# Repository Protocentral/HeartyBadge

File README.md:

# ProtoCentral HeartyBadge

HeartyBadge is simply our popular HeartyPatch single-lead ECG & Heart-rate variability (HRV) monitoring device made into a badge in time for DEFCON 26, where I presented about our HealthyPi open-source patient monitor. We think of HeartyBadge as a ECG and HRV development board, on a badge. 

The following are the main features of the HeartyBadge: 
* Single-lead ECG monitoring with the MAX30003 
* 2 gold-plated pads on the PCB act as electrodes 
* ESP32 with PCB antenna supporting Bluetooth & Wi-Fi 
* 144 APA102 RGB addressable LEDs (most of them in a matrix) 
* On-board Li-Ion battery with charging 
* USB for charging, code upload as well as debugging 

More information is available on our Hackaday project page at: https://hackaday.io/project/160846-heartybadge

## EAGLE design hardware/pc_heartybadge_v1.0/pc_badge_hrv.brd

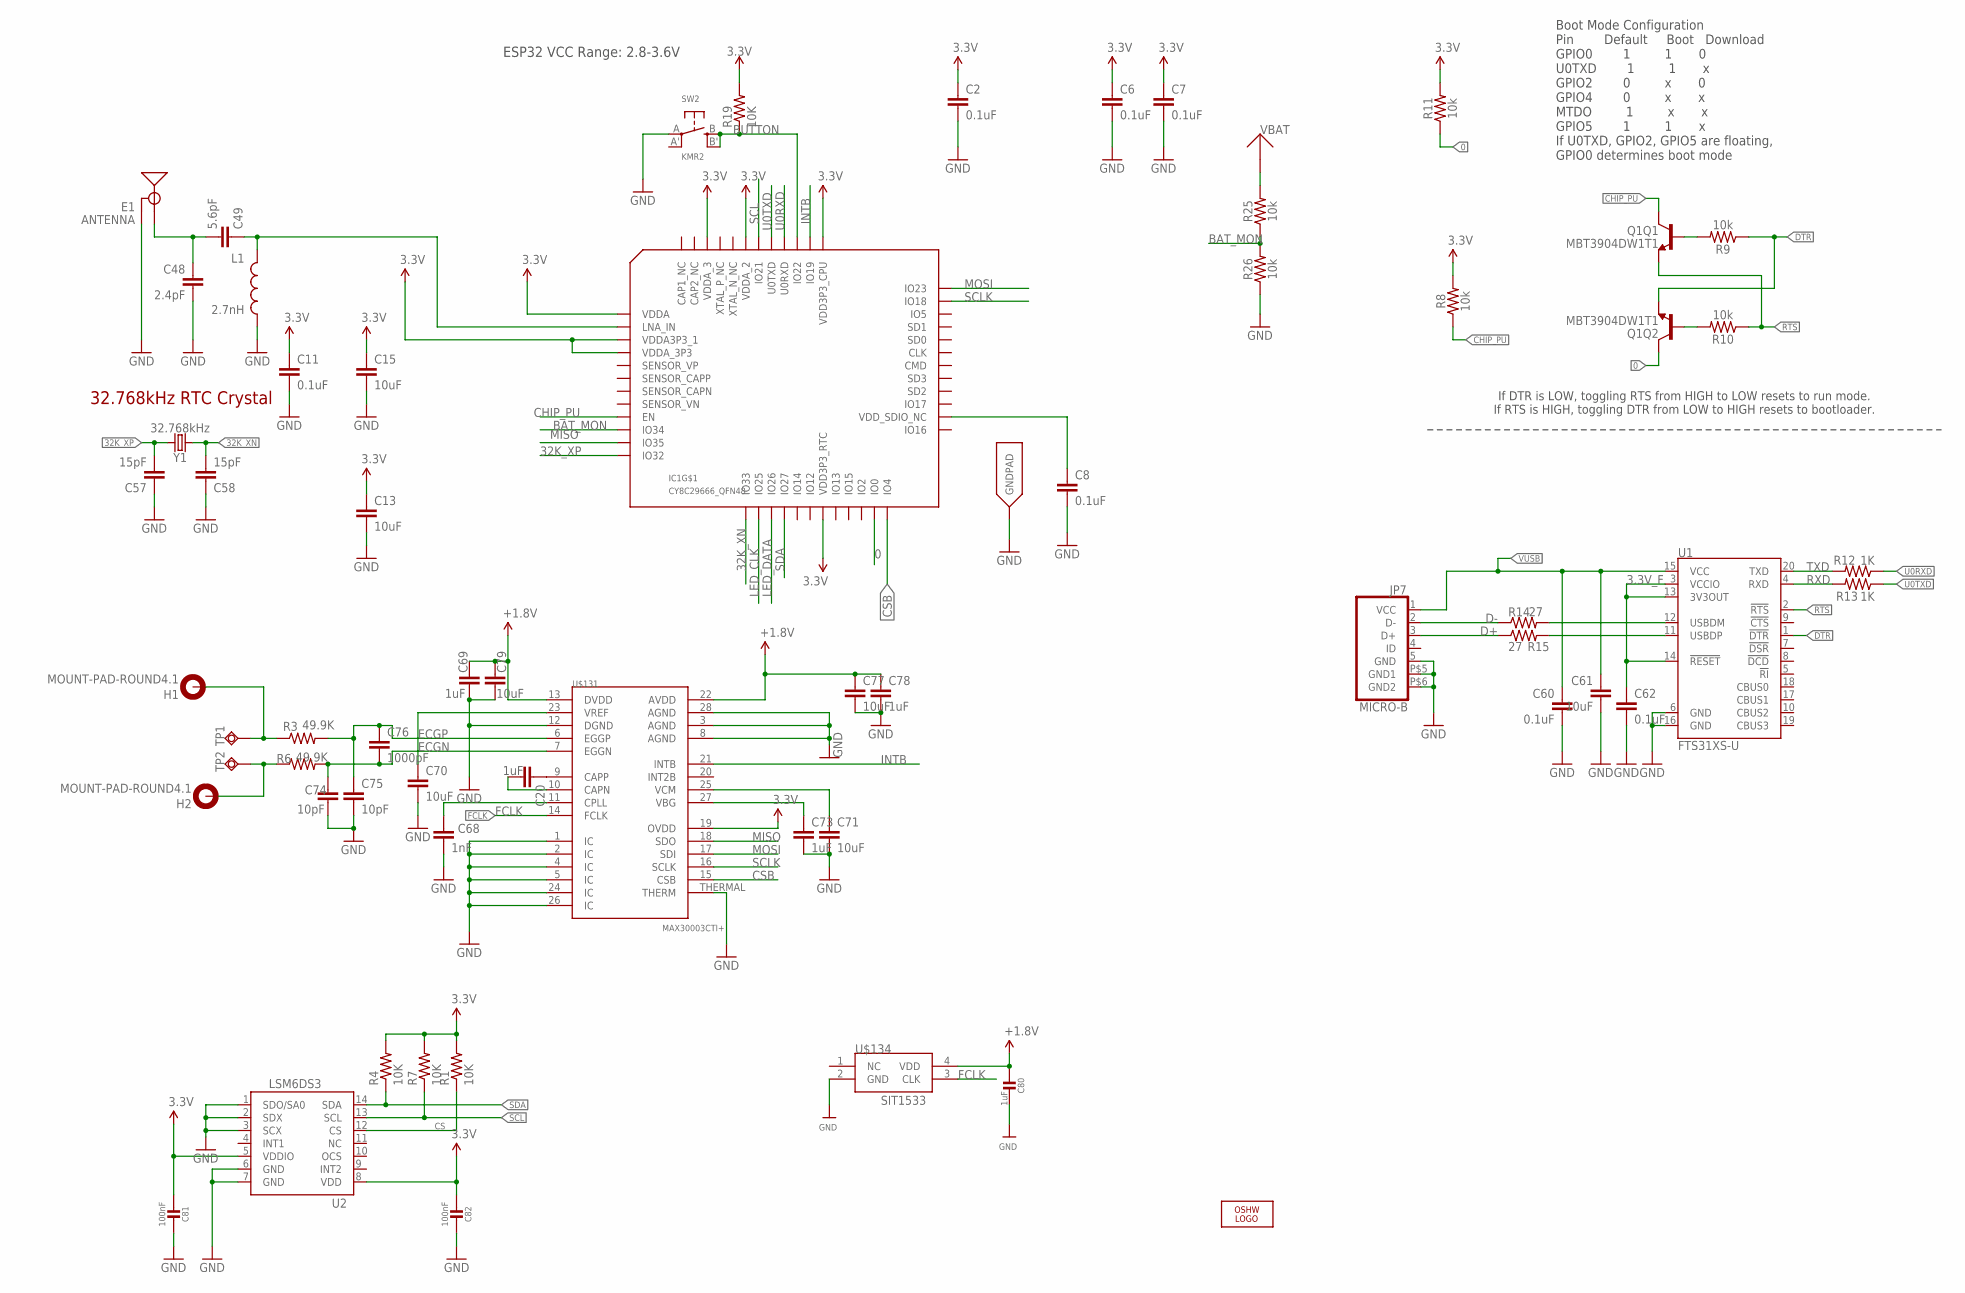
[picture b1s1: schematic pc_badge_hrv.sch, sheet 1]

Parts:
C2, C6, C7, C8, C11: 0.1uF; 0402
C13, C15: 10uF; 0603
C20, C69, C73, C78: 1uF; C0402
C48: 2.4pF; 0603
C49: 5.6pF; 0603
C57, C58: 15pF; 0603
C60, C62: 0.1uF; C0402
C61: 10uF; C0805
C68: 1nF; C0402
C70, C71, C77, C79: 10uF; C0402
C74, C75: 10pF; C0402
C76: 1000pF; C0402
C80: 1uF; _0402
C81, C82: 100nF; _0402
E1: ANTENNA; TRACE_ANTENNA_2.4GHZ_25.7MM_TUNED
H1, H2: MOUNT-PAD-ROUND4.1; 4,1-PAD
IC1: CY8C29666_QFN48; QFN48
JP7: MICRO-B
L1: 2.7nH; 0603
LOGO3: OSHW_LOGO_FILLX0200-NT; OSHW_FILLX200_NOTEXT
Q1: MBT3904DW1T1; SC70-6
R1, R4, R7: 10K; 0402-RES
R3, R6: 49.9K; 0402-RES
R8, R9, R10, R11, R25, R26: 10k; 0603
R12, R13: 1K; R0402
R14, R15: 27; R0402
R19: 10K; R0402
SW2: KMR2; BTN_KMR2_4.6X2.8
TP1, TP2: TPSQTP11R; TP11R
U1: FTS31XS-U; SSOP20_L
U2: LSM6DS3; LGA14L
U$131: MAX30003CTI+; QFN-28
U$134: SIT1533
Y1: 32.768kHz; CRYSTAL-SMD-3.2X1.5MM

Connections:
0: IC1.23 (IO0), Q1.6 (C), R11.1
3.3V: C2.1, C6.1, C7.1, C11.1, C13.1, C15.1, C81.1, C82.1, IC1.1 (VDDA), IC1.3 (VDDA3P3_1), IC1.4 (VDDA_3P3), IC1.19 (VDD3P3_RTC), IC1.37 (VDD3P3_CPU), IC1.43 (VDDA_2), IC1.46 (VDDA_3), R1.2, R4.2, R7.2, R8.2, R11.2, R19.2, U2.5 (VDDIO), U2.8 (VDD), U$131.19 (OVDD); also elsewhere on the board
3.3V_F: C62.1, U1.3 (VCCIO), U1.13 (3V3OUT), U1.14 (!RESET)
32K_XN: C58.2, IC1.13 (IO33), Y1.P$2 (2)
32K_XP: C57.2, IC1.12 (IO32), Y1.P$1 (1)
+1.8V: C69.1, C77.1, C78.1, C79.1, C80.1, U$131.13 (DVDD), U$131.22 (AVDD), U$134.4 (VDD)
BAT_MON: IC1.10 (IO34), R25.1, R26.2
BUTTON: IC1.39 (IO22), R19.1, SW2.B (S), SW2.B' (S1)
CHIP_PU: IC1.9 (EN), Q1.3 (C), R8.1
CS: R1.1, U2.12 (CS)
CSB: IC1.24 (IO4), U$131.15 (CSB)
D+: JP7.3 (D+), R15.1
D-: JP7.2 (D-), R14.1
DTR: Q1.1 (E), R9.1, U1.1 (!DTR)
ECGN: C74.1, C76.2, R6.2, U$131.7 (EGGN)
ECGP: C75.1, C76.1, R3.2, U$131.6 (EGGP)
ECG_N: H2.B4,1, R6.1, TP2.TP
ECG_P: H1.B4,1, R3.1, TP1.TP
FCLK: U$131.14 (FCLK), U$134.3 (CLK)
GND: C2.2, C6.2, C7.2, C8.2, C11.2, C13.2, C15.2, C48.2, C57.1, C58.1, C60.2, C61.2, C62.2, C68.2, C69.2, C70.2, C71.2, C73.2, C74.2, C75.2, C77.2, C78.2, C79.2, C80.2, C81.2, C82.2, E1.GND, E1.GND2 (GND), IC1.EXP (GNDPAD), JP7.5 (GND), JP7.P$5 (GND1), JP7.P$6 (GND2), L1.2, R26.1, SW2.A, U1.6 (GND), U1.16 (GND), U2.1 (SDO/SA0), U2.2 (SDX), U2.3 (SCX), U2.6 (GND), U2.7 (GND), U$131.1 (IC), U$131.2 (IC), U$131.3 (AGND), U$131.4 (IC), U$131.5 (IC), U$131.8 (AGND), U$131.12 (DGND), U$131.24 (IC), U$131.26 (IC), U$131.28 (AGND), U$131.THERMAL (THERM), U$134.2 (GND); also elsewhere on the board
INTB: IC1.38 (IO19), U$131.21 (INTB)
IO12: IC1.18 (IO12)
LED_CLK: IC1.14 (IO25); also elsewhere on the board
LED_DATA: IC1.15 (IO26); also elsewhere on the board
LNA_IN: C49.1, IC1.2 (LNA_IN), L1.1
MISO: IC1.11 (IO35), U$131.18 (SDO)
MOSI: IC1.36 (IO23), U$131.17 (SDI)
unnamed: C8.1, IC1.26 (VDD_SDIO_NC)
unnamed: Q1.5 (B), R9.2
unnamed: Q1.2 (B), R10.2
unnamed: R14.2, U1.12 (USBDM)
unnamed: R15.2, U1.11 (USBDP)
unnamed: C68.1, U$131.11 (CPLL)
unnamed: C20.1, U$131.9 (CAPP)
unnamed: C20.2, U$131.10 (CAPN)
unnamed: C70.1, U$131.23 (VREF)
unnamed: C71.1, U$131.25 (VCM)
unnamed: C73.1, U$131.27 (VBG)
RTS: Q1.4 (E), R10.1, U1.2 (!RTS)
RXD: R13.2, U1.4 (RXD)
SCL: IC1.42 (IO21), R7.1, U2.13 (SCL)
SCLK: IC1.35 (IO18), U$131.16 (SCLK)
SDA: IC1.16 (IO27), R4.1, U2.14 (SDA)
SENSOR_CAPN: IC1.7 (SENSOR_CAPN)
TRACE_ANT2: C48.1, C49.2, E1.ANT (SIGNAL)
TXD: R12.2, U1.20 (TXD)
U0RXD: IC1.40 (U0RXD), R12.1
U0TXD: IC1.41 (U0TXD), R13.1
VBAT: R25.2; also elsewhere on the board
VUSB: C60.1, C61.1, JP7.1 (VCC), U1.15 (VCC); also elsewhere on the board

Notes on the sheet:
Boot Mode Configuration Pin Default Boot Download GPIO0 1 1 0 U0TXD 1 1 x GPIO2 0 x 0 GPIO4 0 x x MTDO 1 x x GPIO5 1 1 x If U0TXD, GPIO2, GPIO5 are floating, GPIO0 determines boot mode
32.768kHz RTC Crystal
ESP32 VCC Range: 2.8-3.6V
If DTR is LOW, toggling RTS from HIGH to LOW resets to run mode. If RTS is HIGH, toggling DTR from LOW to HIGH resets to bootloader.

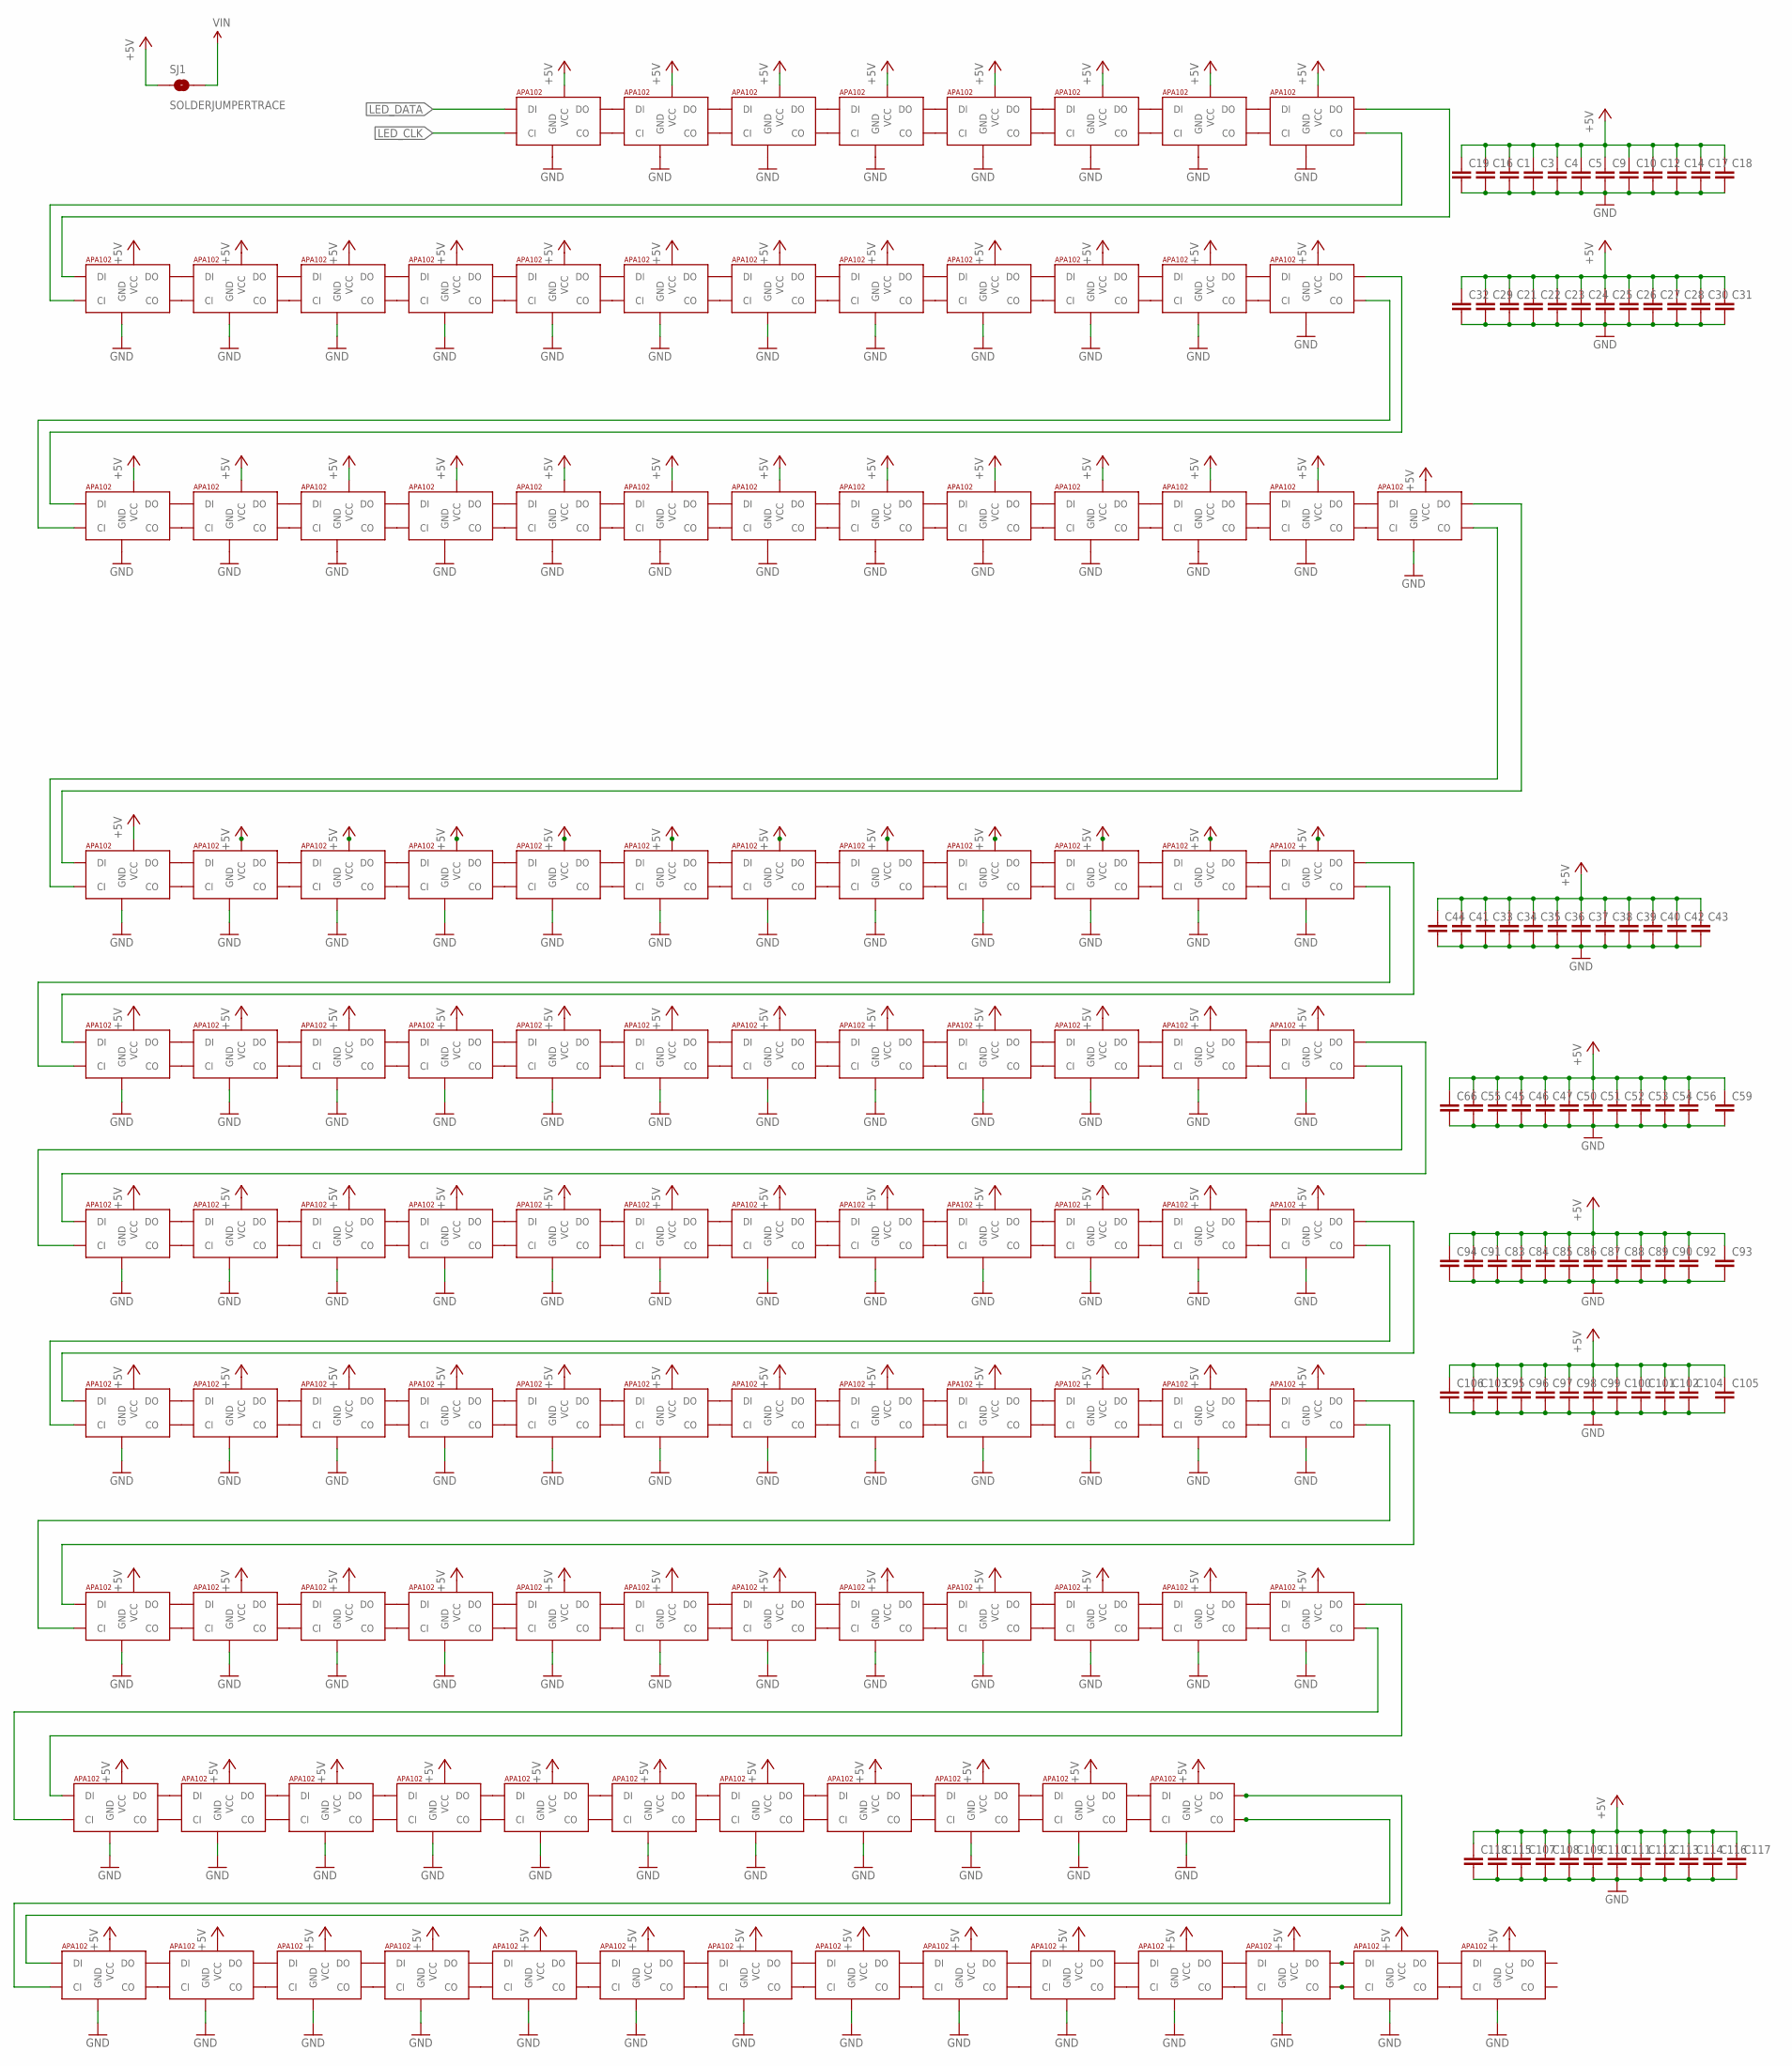
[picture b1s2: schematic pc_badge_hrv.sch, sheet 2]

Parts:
C1, C3, C4, C5, C9, C10, C12, C14, C16, C17, C18, C19, C21, C22, C23, C24, C25, C26, C27, C28, C29, C30, C31, C32, C33, C34, C35, C36, C37, C38, C39, C40, C41, C42, C43, C44, C45, C46, C47, C50, C51, C52, C53, C54, C55, C56, C59, C66, C83, C84, C85, C86, C87, C88, C89, C90, C91, C92, C93, C94, C95, C96, C97, C98, C99, C100, C101, C102, C103, C104, C105, C106, C107, C108, C109, C110, C111, C112, C113, C114, C115, C116, C117, C118: C-EUC0402K; C0402K
SJ1: SOLDERJUMPERTRACE; SJ_2S-TRACE
U$9, U$10, U$11, U$12, U$13, U$14, U$15, U$18, U$19, U$20, U$21, U$22, U$24, U$25, U$27, U$28, U$29, U$30, U$31, U$32, U$33, U$34, U$35, U$36, U$37, U$38, U$39, U$40, U$41, U$42, U$43, U$44, U$45, U$46, U$47, U$48, U$49, U$50, U$51, U$52, U$53, U$54, U$55, U$56, U$57, U$58, U$59, U$60, U$61, U$62, U$63, U$64, U$65, U$66, U$67, U$68, U$69, U$70, U$71, U$72, U$73, U$74, U$75, U$76, U$77, U$78, U$79, U$80, U$81, U$82, U$83, U$84, U$85, U$86, U$87, U$88, U$89, U$90, U$91, U$92, U$93, U$94, U$95, U$96, U$97, U$98, U$99, U$100, U$101, U$102, U$103, U$104, U$105, U$106, U$107, U$108, U$109, U$110, U$111, U$112, U$113, U$114, U$115, U$116, U$117, U$118, U$119, U$120, U$121, U$122, U$123, U$124, U$125, U$126, U$127, U$128, U$129, U$130: APA1022020; APA102_2020

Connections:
+5V: C1.1, C3.1, C4.1, C5.1, C9.1, C10.1, C12.1, C14.1, C16.1, C17.1, C18.1, C19.1, C21.1, C22.1, C23.1, C24.1, C25.1, C26.1, C27.1, C28.1, C29.1, C30.1, C31.1, C32.1, C33.1, C34.1, C35.1, C36.1, C37.1, C38.1, C39.1, C40.1, C41.1, C42.1, C43.1, C44.1, C45.1, C46.1, C47.1, C50.1, C51.1, C52.1, C53.1, C54.1, C55.1, C56.1, C59.1, C66.1, C83.1, C84.1, C85.1, C86.1, C87.1, C88.1, C89.1, C90.1, C91.1, C92.1, C93.1, C94.1, C95.1, C96.1, C97.1, C98.1, C99.1, C100.1, C101.1, C102.1, C103.1, C104.1, C105.1, C106.1, C107.1, C108.1, C109.1, C110.1, C111.1, C112.1, C113.1, C114.1, C115.1, C116.1, C117.1, C118.1, SJ1.1, U$9.V_CC (VCC), U$10.V_CC (VCC), U$11.V_CC (VCC), U$12.V_CC (VCC), U$13.V_CC (VCC), U$14.V_CC (VCC), U$15.V_CC (VCC), U$18.V_CC (VCC), U$19.V_CC (VCC), U$20.V_CC (VCC), U$21.V_CC (VCC), U$22.V_CC (VCC), U$24.V_CC (VCC), U$25.V_CC (VCC), U$27.V_CC (VCC), U$28.V_CC (VCC), U$29.V_CC (VCC), U$30.V_CC (VCC), U$31.V_CC (VCC), U$32.V_CC (VCC), U$33.V_CC (VCC), U$34.V_CC (VCC), U$35.V_CC (VCC), U$36.V_CC (VCC), U$37.V_CC (VCC), U$38.V_CC (VCC), U$39.V_CC (VCC), U$40.V_CC (VCC), U$41.V_CC (VCC), U$42.V_CC (VCC), U$43.V_CC (VCC), U$44.V_CC (VCC), U$45.V_CC (VCC), U$46.V_CC (VCC), U$47.V_CC (VCC), U$48.V_CC (VCC), U$49.V_CC (VCC), U$50.V_CC (VCC), U$51.V_CC (VCC), U$52.V_CC (VCC), U$53.V_CC (VCC), U$54.V_CC (VCC), U$55.V_CC (VCC), U$56.V_CC (VCC), U$57.V_CC (VCC), U$58.V_CC (VCC), U$59.V_CC (VCC), U$60.V_CC (VCC), U$61.V_CC (VCC), U$62.V_CC (VCC), U$63.V_CC (VCC), U$64.V_CC (VCC), U$65.V_CC (VCC), U$66.V_CC (VCC), U$67.V_CC (VCC), U$68.V_CC (VCC), U$69.V_CC (VCC), U$70.V_CC (VCC), U$71.V_CC (VCC), U$72.V_CC (VCC), U$73.V_CC (VCC), U$74.V_CC (VCC), U$75.V_CC (VCC), U$76.V_CC (VCC), U$77.V_CC (VCC), U$78.V_CC (VCC), U$79.V_CC (VCC), U$80.V_CC (VCC), U$81.V_CC (VCC), U$82.V_CC (VCC), U$83.V_CC (VCC), U$84.V_CC (VCC), U$85.V_CC (VCC), U$86.V_CC (VCC), U$87.V_CC (VCC), U$88.V_CC (VCC), U$89.V_CC (VCC), U$90.V_CC (VCC), U$91.V_CC (VCC), U$92.V_CC (VCC), U$93.V_CC (VCC), U$94.V_CC (VCC), U$95.V_CC (VCC), U$96.V_CC (VCC), U$97.V_CC (VCC), U$98.V_CC (VCC), U$99.V_CC (VCC), U$100.V_CC (VCC), U$101.V_CC (VCC), U$102.V_CC (VCC), U$103.V_CC (VCC), U$104.V_CC (VCC), U$105.V_CC (VCC), U$106.V_CC (VCC), U$107.V_CC (VCC), U$108.V_CC (VCC), U$109.V_CC (VCC), U$110.V_CC (VCC), U$111.V_CC (VCC), U$112.V_CC (VCC), U$113.V_CC (VCC), U$114.V_CC (VCC), U$115.V_CC (VCC), U$116.V_CC (VCC), U$117.V_CC (VCC), U$118.V_CC (VCC), U$119.V_CC (VCC), U$120.V_CC (VCC), U$121.V_CC (VCC), U$122.V_CC (VCC), U$123.V_CC (VCC), U$124.V_CC (VCC), U$125.V_CC (VCC), U$126.V_CC (VCC), U$127.V_CC (VCC), U$128.V_CC (VCC), U$129.V_CC (VCC), U$130.V_CC (VCC)
GND: C1.2, C3.2, C4.2, C5.2, C9.2, C10.2, C12.2, C14.2, C16.2, C17.2, C18.2, C19.2, C21.2, C22.2, C23.2, C24.2, C25.2, C26.2, C27.2, C28.2, C29.2, C30.2, C31.2, C32.2, C33.2, C34.2, C35.2, C36.2, C37.2, C38.2, C39.2, C40.2, C41.2, C42.2, C43.2, C44.2, C45.2, C46.2, C47.2, C50.2, C51.2, C52.2, C53.2, C54.2, C55.2, C56.2, C59.2, C66.2, C83.2, C84.2, C85.2, C86.2, C87.2, C88.2, C89.2, C90.2, C91.2, C92.2, C93.2, C94.2, C95.2, C96.2, C97.2, C98.2, C99.2, C100.2, C101.2, C102.2, C103.2, C104.2, C105.2, C106.2, C107.2, C108.2, C109.2, C110.2, C111.2, C112.2, C113.2, C114.2, C115.2, C116.2, C117.2, C118.2, U$9.GND, U$10.GND, U$11.GND, U$12.GND, U$13.GND, U$14.GND, U$15.GND, U$18.GND, U$19.GND, U$20.GND, U$21.GND, U$22.GND, U$24.GND, U$25.GND, U$27.GND, U$28.GND, U$29.GND, U$30.GND, U$31.GND, U$32.GND, U$33.GND, U$34.GND, U$35.GND, U$36.GND, U$37.GND, U$38.GND, U$39.GND, U$40.GND, U$41.GND, U$42.GND, U$43.GND, U$44.GND, U$45.GND, U$46.GND, U$47.GND, U$48.GND, U$49.GND, U$50.GND, U$51.GND, U$52.GND, U$53.GND, U$54.GND, U$55.GND, U$56.GND, U$57.GND, U$58.GND, U$59.GND, U$60.GND, U$61.GND, U$62.GND, U$63.GND, U$64.GND, U$65.GND, U$66.GND, U$67.GND, U$68.GND, U$69.GND, U$70.GND, U$71.GND, U$72.GND, U$73.GND, U$74.GND, U$75.GND, U$76.GND, U$77.GND, U$78.GND, U$79.GND, U$80.GND, U$81.GND, U$82.GND, U$83.GND, U$84.GND, U$85.GND, U$86.GND, U$87.GND, U$88.GND, U$89.GND, U$90.GND, U$91.GND, U$92.GND, U$93.GND, U$94.GND, U$95.GND, U$96.GND, U$97.GND, U$98.GND, U$99.GND, U$100.GND, U$101.GND, U$102.GND, U$103.GND, U$104.GND, U$105.GND, U$106.GND, U$107.GND, U$108.GND, U$109.GND, U$110.GND, U$111.GND, U$112.GND, U$113.GND, U$114.GND, U$115.GND, U$116.GND, U$117.GND, U$118.GND, U$119.GND, U$120.GND, U$121.GND, U$122.GND, U$123.GND, U$124.GND, U$125.GND, U$126.GND, U$127.GND, U$128.GND, U$129.GND, U$130.GND; also elsewhere on the board
LED_CLK: U$9.C_IN (CI); also elsewhere on the board
LED_DATA: U$9.D_IN (DI); also elsewhere on the board
unnamed: U$104.D_OUT (DO), U$119.D_IN (DI)
unnamed: U$104.CL_OUT (CO), U$119.C_IN (CI)
unnamed: U$9.D_OUT (DO), U$10.D_IN (DI)
unnamed: U$9.CL_OUT (CO), U$10.C_IN (CI)
unnamed: U$11.D_OUT (DO), U$12.D_IN (DI)
unnamed: U$11.CL_OUT (CO), U$12.C_IN (CI)
unnamed: U$12.D_OUT (DO), U$13.D_IN (DI)
unnamed: U$12.CL_OUT (CO), U$13.C_IN (CI)
unnamed: U$13.D_OUT (DO), U$14.D_IN (DI)
unnamed: U$13.CL_OUT (CO), U$14.C_IN (CI)
unnamed: U$14.D_OUT (DO), U$15.D_IN (DI)
unnamed: U$14.CL_OUT (CO), U$15.C_IN (CI)
unnamed: U$15.D_OUT (DO), U$18.D_IN (DI)
unnamed: U$15.CL_OUT (CO), U$18.C_IN (CI)
unnamed: U$10.D_OUT (DO), U$11.D_IN (DI)
unnamed: U$10.CL_OUT (CO), U$11.C_IN (CI)
unnamed: U$19.D_OUT (DO), U$20.D_IN (DI)
unnamed: U$19.CL_OUT (CO), U$20.C_IN (CI)
unnamed: U$20.D_OUT (DO), U$21.D_IN (DI)
unnamed: U$20.CL_OUT (CO), U$21.C_IN (CI)
unnamed: U$21.D_OUT (DO), U$22.D_IN (DI)
unnamed: U$21.CL_OUT (CO), U$22.C_IN (CI)
unnamed: U$22.D_OUT (DO), U$24.D_IN (DI)
unnamed: U$22.CL_OUT (CO), U$24.C_IN (CI)
unnamed: U$24.D_OUT (DO), U$25.D_IN (DI)
unnamed: U$24.CL_OUT (CO), U$25.C_IN (CI)
unnamed: U$27.D_OUT (DO), U$28.D_IN (DI)
unnamed: U$27.CL_OUT (CO), U$28.C_IN (CI)
unnamed: U$28.D_OUT (DO), U$29.D_IN (DI)
unnamed: U$28.CL_OUT (CO), U$29.C_IN (CI)
unnamed: U$29.D_OUT (DO), U$30.D_IN (DI)
unnamed: U$29.CL_OUT (CO), U$30.C_IN (CI)
unnamed: U$30.D_OUT (DO), U$31.D_IN (DI)
unnamed: U$30.CL_OUT (CO), U$31.C_IN (CI)
unnamed: U$119.D_OUT (DO), U$120.D_IN (DI)
unnamed: U$119.CL_OUT (CO), U$120.C_IN (CI)
unnamed: U$25.D_OUT (DO), U$27.D_IN (DI)
unnamed: U$25.CL_OUT (CO), U$27.C_IN (CI)
unnamed: U$33.D_OUT (DO), U$34.D_IN (DI)
unnamed: U$33.CL_OUT (CO), U$34.C_IN (CI)
unnamed: U$34.D_OUT (DO), U$35.D_IN (DI)
unnamed: U$34.CL_OUT (CO), U$35.C_IN (CI)
unnamed: U$35.D_OUT (DO), U$36.D_IN (DI)
unnamed: U$35.CL_OUT (CO), U$36.C_IN (CI)
unnamed: U$36.D_OUT (DO), U$37.D_IN (DI)
unnamed: U$36.CL_OUT (CO), U$37.C_IN (CI)
unnamed: U$37.D_OUT (DO), U$38.D_IN (DI)
unnamed: U$37.CL_OUT (CO), U$38.C_IN (CI)
unnamed: U$39.D_OUT (DO), U$40.D_IN (DI)
unnamed: U$39.CL_OUT (CO), U$40.C_IN (CI)
unnamed: U$40.D_OUT (DO), U$41.D_IN (DI)
unnamed: U$40.CL_OUT (CO), U$41.C_IN (CI)
unnamed: U$41.D_OUT (DO), U$42.D_IN (DI)
unnamed: U$41.CL_OUT (CO), U$42.C_IN (CI)
unnamed: U$42.D_OUT (DO), U$43.D_IN (DI)
unnamed: U$42.CL_OUT (CO), U$43.C_IN (CI)
unnamed: U$43.D_OUT (DO), U$44.D_IN (DI)
unnamed: U$43.CL_OUT (CO), U$44.C_IN (CI)
unnamed: U$38.D_OUT (DO), U$39.D_IN (DI)
unnamed: U$38.CL_OUT (CO), U$39.C_IN (CI)
unnamed: U$45.D_OUT (DO), U$46.D_IN (DI)
unnamed: U$45.CL_OUT (CO), U$46.C_IN (CI)
unnamed: U$46.D_OUT (DO), U$47.D_IN (DI)
unnamed: U$46.CL_OUT (CO), U$47.C_IN (CI)
unnamed: U$47.D_OUT (DO), U$48.D_IN (DI)
unnamed: U$47.CL_OUT (CO), U$48.C_IN (CI)
unnamed: U$48.D_OUT (DO), U$49.D_IN (DI)
unnamed: U$48.CL_OUT (CO), U$49.C_IN (CI)
unnamed: U$49.D_OUT (DO), U$50.D_IN (DI)
unnamed: U$49.CL_OUT (CO), U$50.C_IN (CI)
unnamed: U$51.D_OUT (DO), U$52.D_IN (DI)
unnamed: U$51.CL_OUT (CO), U$52.C_IN (CI)
unnamed: U$52.D_OUT (DO), U$53.D_IN (DI)
unnamed: U$52.CL_OUT (CO), U$53.C_IN (CI)
unnamed: U$53.D_OUT (DO), U$54.D_IN (DI)
unnamed: U$53.CL_OUT (CO), U$54.C_IN (CI)
unnamed: U$54.D_OUT (DO), U$55.D_IN (DI)
unnamed: U$54.CL_OUT (CO), U$55.C_IN (CI)
unnamed: U$55.D_OUT (DO), U$56.D_IN (DI)
unnamed: U$55.CL_OUT (CO), U$56.C_IN (CI)
unnamed: U$50.D_OUT (DO), U$51.D_IN (DI)
unnamed: U$50.CL_OUT (CO), U$51.C_IN (CI)
unnamed: U$18.D_OUT (DO), U$19.D_IN (DI)
unnamed: U$18.CL_OUT (CO), U$19.C_IN (CI)
unnamed: U$32.D_OUT (DO), U$33.D_IN (DI)
unnamed: U$32.CL_OUT (CO), U$33.C_IN (CI)
unnamed: U$44.CL_OUT (CO), U$45.C_IN (CI)
unnamed: U$44.D_OUT (DO), U$45.D_IN (DI)
unnamed: U$57.D_OUT (DO), U$58.D_IN (DI)
unnamed: U$57.CL_OUT (CO), U$58.C_IN (CI)
unnamed: U$58.D_OUT (DO), U$59.D_IN (DI)
unnamed: U$58.CL_OUT (CO), U$59.C_IN (CI)
unnamed: U$59.D_OUT (DO), U$60.D_IN (DI)
unnamed: U$59.CL_OUT (CO), U$60.C_IN (CI)
unnamed: U$60.D_OUT (DO), U$61.D_IN (DI)
unnamed: U$60.CL_OUT (CO), U$61.C_IN (CI)
unnamed: U$61.D_OUT (DO), U$62.D_IN (DI)
unnamed: U$61.CL_OUT (CO), U$62.C_IN (CI)
unnamed: U$63.D_OUT (DO), U$64.D_IN (DI)
unnamed: U$63.CL_OUT (CO), U$64.C_IN (CI)
unnamed: U$64.D_OUT (DO), U$65.D_IN (DI)
unnamed: U$64.CL_OUT (CO), U$65.C_IN (CI)
unnamed: U$65.D_OUT (DO), U$66.D_IN (DI)
unnamed: U$65.CL_OUT (CO), U$66.C_IN (CI)
unnamed: U$66.D_OUT (DO), U$67.D_IN (DI)
unnamed: U$66.CL_OUT (CO), U$67.C_IN (CI)
unnamed: U$67.D_OUT (DO), U$68.D_IN (DI)
unnamed: U$67.CL_OUT (CO), U$68.C_IN (CI)
unnamed: U$62.D_OUT (DO), U$63.D_IN (DI)
unnamed: U$62.CL_OUT (CO), U$63.C_IN (CI)
unnamed: U$56.CL_OUT (CO), U$57.C_IN (CI)
unnamed: U$56.D_OUT (DO), U$57.D_IN (DI)
unnamed: U$69.D_OUT (DO), U$70.D_IN (DI)
unnamed: U$69.CL_OUT (CO), U$70.C_IN (CI)
unnamed: U$70.D_OUT (DO), U$71.D_IN (DI)
unnamed: U$70.CL_OUT (CO), U$71.C_IN (CI)
unnamed: U$71.D_OUT (DO), U$72.D_IN (DI)
unnamed: U$71.CL_OUT (CO), U$72.C_IN (CI)
unnamed: U$72.D_OUT (DO), U$73.D_IN (DI)
unnamed: U$72.CL_OUT (CO), U$73.C_IN (CI)
unnamed: U$73.D_OUT (DO), U$74.D_IN (DI)
unnamed: U$73.CL_OUT (CO), U$74.C_IN (CI)
unnamed: U$75.D_OUT (DO), U$76.D_IN (DI)
unnamed: U$75.CL_OUT (CO), U$76.C_IN (CI)
unnamed: U$76.D_OUT (DO), U$77.D_IN (DI)
unnamed: U$76.CL_OUT (CO), U$77.C_IN (CI)
unnamed: U$77.D_OUT (DO), U$78.D_IN (DI)
unnamed: U$77.CL_OUT (CO), U$78.C_IN (CI)
unnamed: U$78.D_OUT (DO), U$79.D_IN (DI)
unnamed: U$78.CL_OUT (CO), U$79.C_IN (CI)
unnamed: U$79.D_OUT (DO), U$80.D_IN (DI)
unnamed: U$79.CL_OUT (CO), U$80.C_IN (CI)
unnamed: U$74.D_OUT (DO), U$75.D_IN (DI)
unnamed: U$74.CL_OUT (CO), U$75.C_IN (CI)
unnamed: U$68.CL_OUT (CO), U$69.C_IN (CI)
unnamed: U$68.D_OUT (DO), U$69.D_IN (DI)
unnamed: U$81.D_OUT (DO), U$82.D_IN (DI)
unnamed: U$81.CL_OUT (CO), U$82.C_IN (CI)
unnamed: U$82.D_OUT (DO), U$83.D_IN (DI)
unnamed: U$82.CL_OUT (CO), U$83.C_IN (CI)
unnamed: U$83.D_OUT (DO), U$84.D_IN (DI)
unnamed: U$83.CL_OUT (CO), U$84.C_IN (CI)
unnamed: U$84.D_OUT (DO), U$85.D_IN (DI)
unnamed: U$84.CL_OUT (CO), U$85.C_IN (CI)
unnamed: U$85.D_OUT (DO), U$86.D_IN (DI)
unnamed: U$85.CL_OUT (CO), U$86.C_IN (CI)
unnamed: U$87.D_OUT (DO), U$88.D_IN (DI)
unnamed: U$87.CL_OUT (CO), U$88.C_IN (CI)
unnamed: U$88.D_OUT (DO), U$89.D_IN (DI)
unnamed: U$88.CL_OUT (CO), U$89.C_IN (CI)
unnamed: U$89.D_OUT (DO), U$90.D_IN (DI)
unnamed: U$89.CL_OUT (CO), U$90.C_IN (CI)
unnamed: U$90.D_OUT (DO), U$91.D_IN (DI)
unnamed: U$90.CL_OUT (CO), U$91.C_IN (CI)
unnamed: U$91.D_OUT (DO), U$92.D_IN (DI)
unnamed: U$91.CL_OUT (CO), U$92.C_IN (CI)
unnamed: U$86.D_OUT (DO), U$87.D_IN (DI)
unnamed: U$86.CL_OUT (CO), U$87.C_IN (CI)
unnamed: U$80.CL_OUT (CO), U$81.C_IN (CI)
unnamed: U$80.D_OUT (DO), U$81.D_IN (DI)
unnamed: U$93.D_OUT (DO), U$94.D_IN (DI)
unnamed: U$93.CL_OUT (CO), U$94.C_IN (CI)
unnamed: U$94.D_OUT (DO), U$95.D_IN (DI)
unnamed: U$94.CL_OUT (CO), U$95.C_IN (CI)
unnamed: U$95.D_OUT (DO), U$96.D_IN (DI)
unnamed: U$95.CL_OUT (CO), U$96.C_IN (CI)
unnamed: U$96.D_OUT (DO), U$97.D_IN (DI)
unnamed: U$96.CL_OUT (CO), U$97.C_IN (CI)
unnamed: U$97.D_OUT (DO), U$98.D_IN (DI)
unnamed: U$97.CL_OUT (CO), U$98.C_IN (CI)
unnamed: U$99.D_OUT (DO), U$100.D_IN (DI)
unnamed: U$99.CL_OUT (CO), U$100.C_IN (CI)
unnamed: U$100.D_OUT (DO), U$101.D_IN (DI)
unnamed: U$100.CL_OUT (CO), U$101.C_IN (CI)
unnamed: U$101.D_OUT (DO), U$102.D_IN (DI)
unnamed: U$101.CL_OUT (CO), U$102.C_IN (CI)
unnamed: U$102.D_OUT (DO), U$103.D_IN (DI)
unnamed: U$102.CL_OUT (CO), U$103.C_IN (CI)
unnamed: U$120.D_OUT (DO), U$121.D_IN (DI)
unnamed: U$120.CL_OUT (CO), U$121.C_IN (CI)
unnamed: U$98.D_OUT (DO), U$99.D_IN (DI)
unnamed: U$98.CL_OUT (CO), U$99.C_IN (CI)
unnamed: U$105.D_OUT (DO), U$106.D_IN (DI)
unnamed: U$105.CL_OUT (CO), U$106.C_IN (CI)
unnamed: U$106.D_OUT (DO), U$107.D_IN (DI)
unnamed: U$106.CL_OUT (CO), U$107.C_IN (CI)
unnamed: U$107.D_OUT (DO), U$108.D_IN (DI)
unnamed: U$107.CL_OUT (CO), U$108.C_IN (CI)
unnamed: U$108.D_OUT (DO), U$109.D_IN (DI)
unnamed: U$108.CL_OUT (CO), U$109.C_IN (CI)
unnamed: U$109.D_OUT (DO), U$110.D_IN (DI)
unnamed: U$109.CL_OUT (CO), U$110.C_IN (CI)
unnamed: U$111.D_OUT (DO), U$112.D_IN (DI)
unnamed: U$111.CL_OUT (CO), U$112.C_IN (CI)
unnamed: U$112.D_OUT (DO), U$113.D_IN (DI)
unnamed: U$112.CL_OUT (CO), U$113.C_IN (CI)
unnamed: U$113.D_OUT (DO), U$114.D_IN (DI)
unnamed: U$113.CL_OUT (CO), U$114.C_IN (CI)
unnamed: U$114.D_OUT (DO), U$115.D_IN (DI)
unnamed: U$114.CL_OUT (CO), U$115.C_IN (CI)
unnamed: U$115.D_OUT (DO), U$116.D_IN (DI)
unnamed: U$115.CL_OUT (CO), U$116.C_IN (CI)
unnamed: U$110.D_OUT (DO), U$111.D_IN (DI)
unnamed: U$110.CL_OUT (CO), U$111.C_IN (CI)
unnamed: U$92.CL_OUT (CO), U$93.C_IN (CI)
unnamed: U$92.D_OUT (DO), U$93.D_IN (DI)
unnamed: U$103.CL_OUT (CO), U$105.C_IN (CI)
unnamed: U$103.D_OUT (DO), U$105.D_IN (DI)
unnamed: U$117.D_OUT (DO), U$118.D_IN (DI)
unnamed: U$117.CL_OUT (CO), U$118.C_IN (CI)
unnamed: U$121.D_OUT (DO), U$122.D_IN (DI)
unnamed: U$121.CL_OUT (CO), U$122.C_IN (CI)
unnamed: U$116.D_OUT (DO), U$117.D_IN (DI)
unnamed: U$116.CL_OUT (CO), U$117.C_IN (CI)
unnamed: U$122.D_OUT (DO), U$123.D_IN (DI)
unnamed: U$122.CL_OUT (CO), U$123.C_IN (CI)
unnamed: U$124.D_OUT (DO), U$125.D_IN (DI)
unnamed: U$124.CL_OUT (CO), U$125.C_IN (CI)
unnamed: U$125.D_OUT (DO), U$126.D_IN (DI)
unnamed: U$125.CL_OUT (CO), U$126.C_IN (CI)
unnamed: U$126.D_OUT (DO), U$127.D_IN (DI)
unnamed: U$126.CL_OUT (CO), U$127.C_IN (CI)
unnamed: U$127.D_OUT (DO), U$128.D_IN (DI)
unnamed: U$127.CL_OUT (CO), U$128.C_IN (CI)
unnamed: U$128.D_OUT (DO), U$129.D_IN (DI)
unnamed: U$128.CL_OUT (CO), U$129.C_IN (CI)
unnamed: U$123.D_OUT (DO), U$124.D_IN (DI)
unnamed: U$123.CL_OUT (CO), U$124.C_IN (CI)
unnamed: U$31.D_OUT (DO), U$130.D_IN (DI)
unnamed: U$31.CL_OUT (CO), U$130.C_IN (CI)
unnamed: U$104.C_IN (CI), U$130.CL_OUT (CO)
unnamed: U$104.D_IN (DI), U$130.D_OUT (DO)
unnamed: U$32.D_IN (DI), U$129.D_OUT (DO)
unnamed: U$32.C_IN (CI), U$129.CL_OUT (CO)
VIN: SJ1.2; also elsewhere on the board

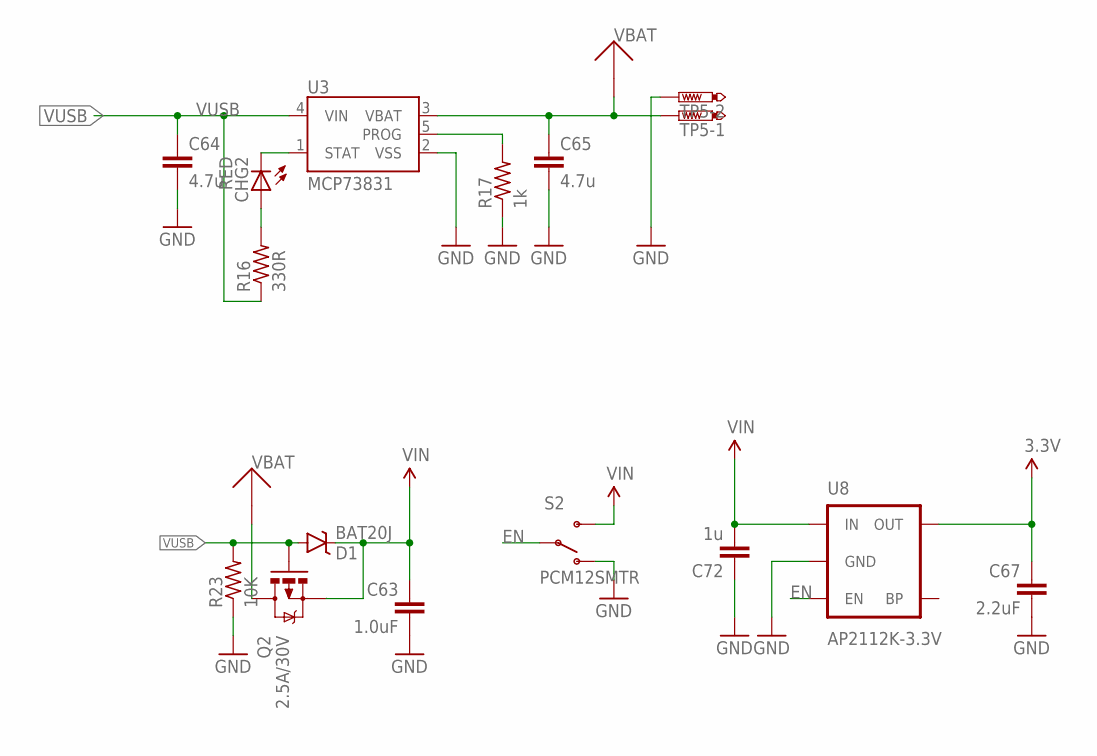
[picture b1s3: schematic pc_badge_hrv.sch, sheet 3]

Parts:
C63: 1.0uF; C0402
C64, C65: 4.7u; C0805
C67: 2.2uF; C0402
C72: 1u; C0402
CHG2: RED; CHIPLED_0603
D1: BAT20J; SOD-323
Q2: 2.5A/30V; SOT23-3
R16: 330R; R0402
R17: 1k; R0402
R23: 10K; R0402
S2: PCM12SMTR; SWITCH-SPST-SMD-A
TP5: PTR2; P2-38-17
U3: MCP73831; SOT23-5
U8: AP2112K-3.3V; SOT23-5

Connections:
3.3V: C67.1, U8.5 (OUT); also elsewhere on the board
EN: S2.2, U8.3 (EN)
GND: C63.2, C64.2, C65.2, C67.2, C72.1, R17.1, R23.1, S2.1 (O), TP5.TP-2, U3.2 (VSS), U8.2 (GND); also elsewhere on the board
unnamed: CHG2.C, U3.1 (STAT)
unnamed: CHG2.A, R16.2
unnamed: R17.2, U3.5 (PROG)
VBAT: C65.1, Q2.3 (D), TP5.TP-1, U3.3 (VBAT); also elsewhere on the board
VIN: C63.1, C72.2, D1.C, Q2.2 (S), S2.3 (S), U8.1 (IN); also elsewhere on the board
VUSB: C64.1, D1.A, Q2.1 (G), R16.1, R23.2, U3.4 (VIN); also elsewhere on the board

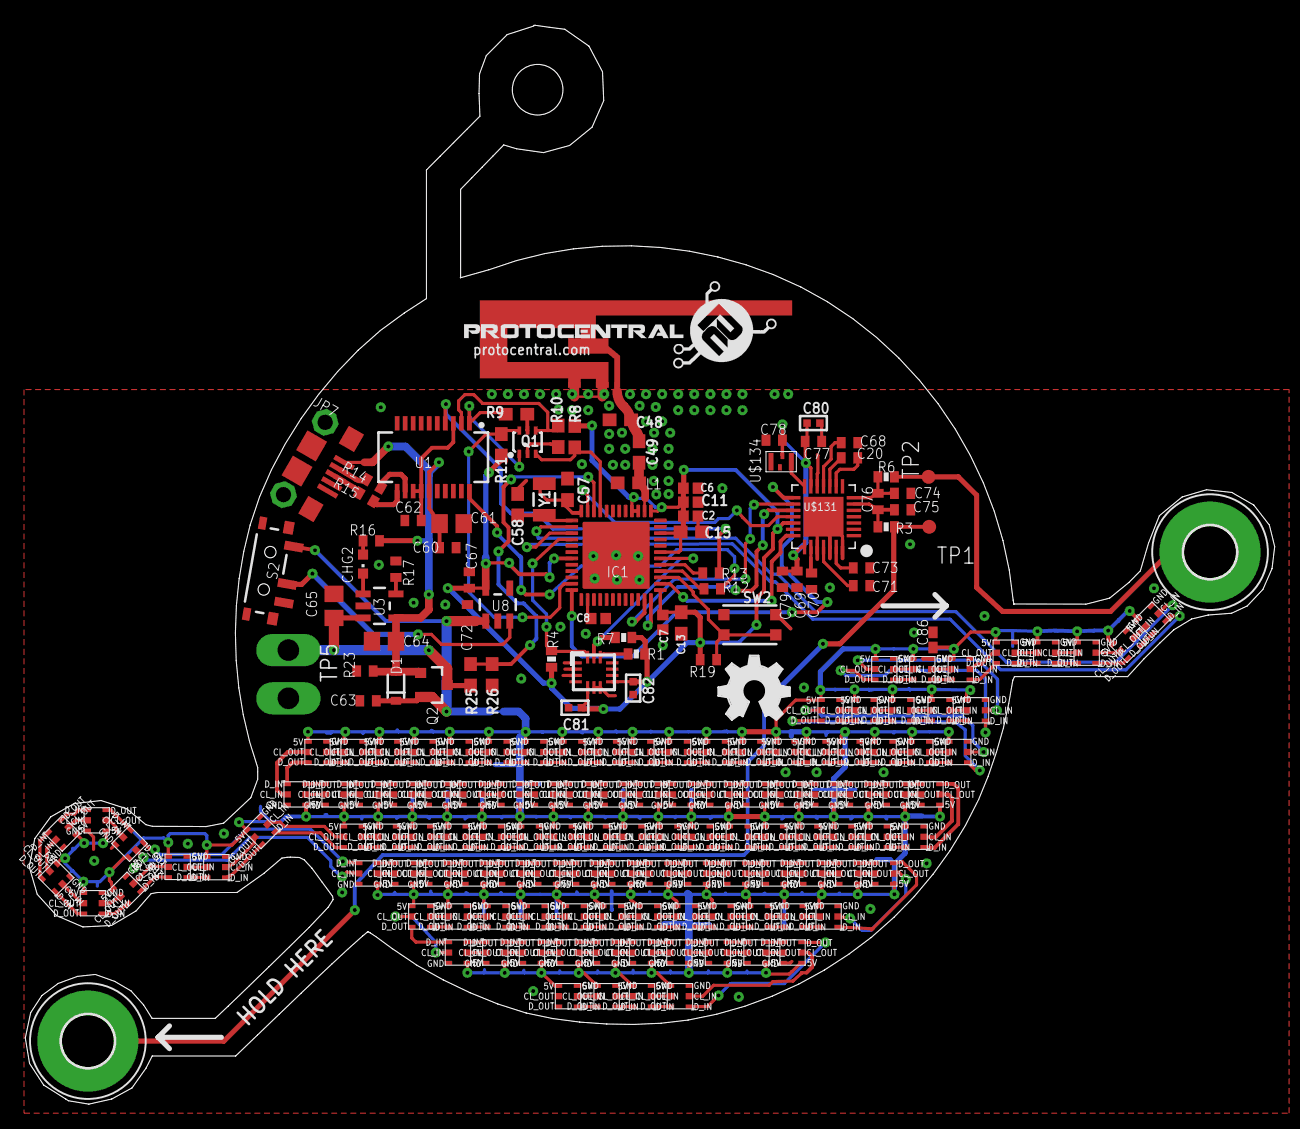
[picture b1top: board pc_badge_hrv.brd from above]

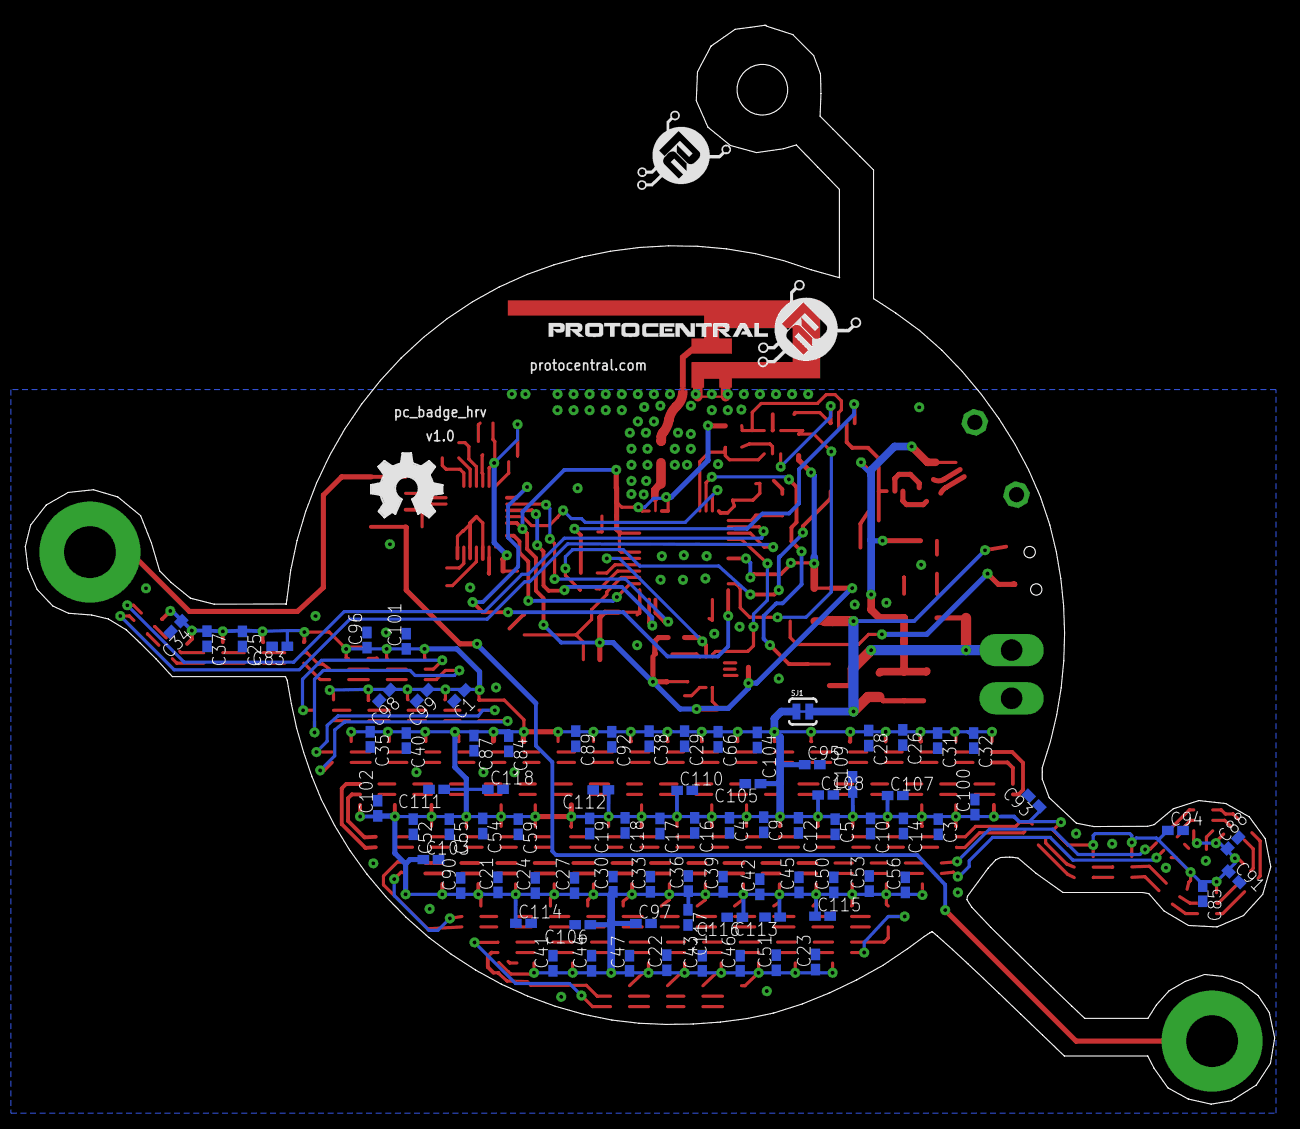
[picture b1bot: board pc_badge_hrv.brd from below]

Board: 4 copper layers, 98.8 x 85.3 mm, 283 parts (87 on the bottom side), 288 nets.

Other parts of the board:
LOGO2: OSHW_LOGO_FILLX0200-NT; OSHW_FILLX200_NOTEXT
U$1, U$26: PROTY_LOGO_WITH_TEXT; PROTY_WITH_TEXT@1
U$6: LOGO-PROTY

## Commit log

2018-09-01 Added all basic files - firmware and hardware

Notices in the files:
parts and their libraries:
SparkFun-Capacitors: Licensing: Creative Commons ShareAlike 4.0 International - https://creativecommons.org/licenses/by-sa/4.0
SparkFun-DigitalIC: Licensing: CC v3.0 Share-Alike You are welcome to use this library for commercial purposes.
